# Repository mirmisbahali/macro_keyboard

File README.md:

# STM32 Macro Keyboard

A custom 6-key macro keyboard built from scratch custom written bare-metal STM32 firmware, hand-drawn schematics, and a PCB designed in KiCAD. No Arduino. No HAL. Just registers, datasheets, and stubbornness.

> **Status:** Hardware design in progress

---

*PCB layout and routing in progress.*

*Wiring is completed — schematic still needs to be made neat and tidy.*

<!-- Add photo of assembled board here -->
<!--  -->

---

## Why

I am learning to design STM32-based hardware - from choosing a microcontroller and designing the PCB, to writing drivers from scratch in register-level C.

## Hardware

| Item | Detail |
|---|---|
| MCU | STM32F072CBTx — Cortex-M0, 48 MHz, 128 KB flash, LQFP-48 |
| Key matrix | 6 switches with diode-per-key (1N4148W) |
| Power | 3.3 V core, ferrite bead on analog rail (VDDA), decoupling on all supply pins |
| Programming | USB DFU via BOOT0 SPDT switch — no debug probe needed |
| EDA tool | KiCAD 10.0 |

---

## Requirements

Requirements follow the systems engineering convention: **shall** = mandatory, **should** = desired.

### SYS — System
| ID | Requirement |
|---|---|
| SYS-01 | The device shall enumerate as a USB HID keyboard on any host OS without requiring driver installation. |
| SYS-02 | The device shall be powered entirely from the USB bus (5 V, ≤ 100 mA). |
| SYS-03 | The device shall support a minimum of 6 independently programmable macro keys. |
| SYS-04 | The device firmware shall be updatable via USB without a hardware debug probe. |
| SYS-05 | All firmware shall be written in register-level C with no vendor HAL or Arduino abstractions. |

### HW — Hardware
| ID | Requirement |
|---|---|
| HW-01 | The MCU core supply (VDD) shall be 3.3 V ± 5%. |
| HW-02 | Each VDD, VDDA, VBAT, and VSSIO2 supply pin shall have a dedicated decoupling capacitor placed within 2 mm of the pin. |
| HW-03 | VDDA shall be filtered from VDD using a ferrite bead to reduce digital noise on the analog supply. |
| HW-04 | Each key switch shall have a dedicated series diode to prevent ghosting in the key matrix. |
| HW-05 | The BOOT0 pin shall be switchable between VDD and GND via an SPDT switch to allow toggling between DFU programming mode and normal run mode. |
| HW-06 | The PCB shall pass KiCAD DRC with zero errors before submission for fabrication. |

### FW — Firmware
| ID | Requirement |
|---|---|
| FW-01 | The firmware shall configure the system clock to 48 MHz using the internal PLL before any peripheral initialisation. |
| FW-02 | The key scan loop shall debounce each key with a settling time of ≤ 5 ms. |
| FW-03 | The firmware shall report a key press to the USB host within 10 ms of a physical key actuation. |
| FW-04 | Macro key mappings shall be stored in non-volatile flash and survive a power cycle. |
| FW-05 | The firmware shall implement the USB HID boot-protocol keyboard descriptor to ensure compatibility with BIOS/UEFI environments. |

### VER — Verification
| ID | Requirement | Method |
|---|---|---|
| VER-01 | All supply rails measure within tolerance at board bring-up. | Test — multimeter |
| VER-02 | Device enumerates as HID keyboard on Windows, macOS, and Linux. | Test — plug in, check device manager |
| VER-03 | Every key registers a unique, correct HID keycode. | Test — key tester utility |
| VER-04 | Firmware can be flashed via DFU using only the BOOT0 switch and a USB cable. | Demonstration |
| VER-05 | Key mappings persist across power cycles. | Test — assign macro, power cycle, verify |
| VER-06 | PCB DRC passes with zero errors. | Analysis — KiCAD DRC report |

---

<details>
<summary><strong>Roadmap</strong></summary>

### Electronics
- [x] MCU symbol + footprint
- [x] Decoupling capacitors (VBAT, VDD, VDDA, VSSIO2)
- [x] BOOT0 SPDT switch for programming / run mode toggle
- [ ] USB data lines + ESD protection
- [ ] USB power input + 3.3 V regulator
- [ ] Key switch matrix (complete all 6 keys)
- [ ] PCB layout and routing
- [ ] DRC pass → Gerber export → fabrication

### Firmware
- [ ] Bare-metal project setup (linker script, startup file)
- [ ] System clock → 48 MHz via PLL
- [ ] GPIO driver — key matrix scan
- [ ] USB HID descriptor (boot-protocol keyboard)
- [ ] Key debounce
- [ ] Macro layer + flash storage for mappings

</details>

---

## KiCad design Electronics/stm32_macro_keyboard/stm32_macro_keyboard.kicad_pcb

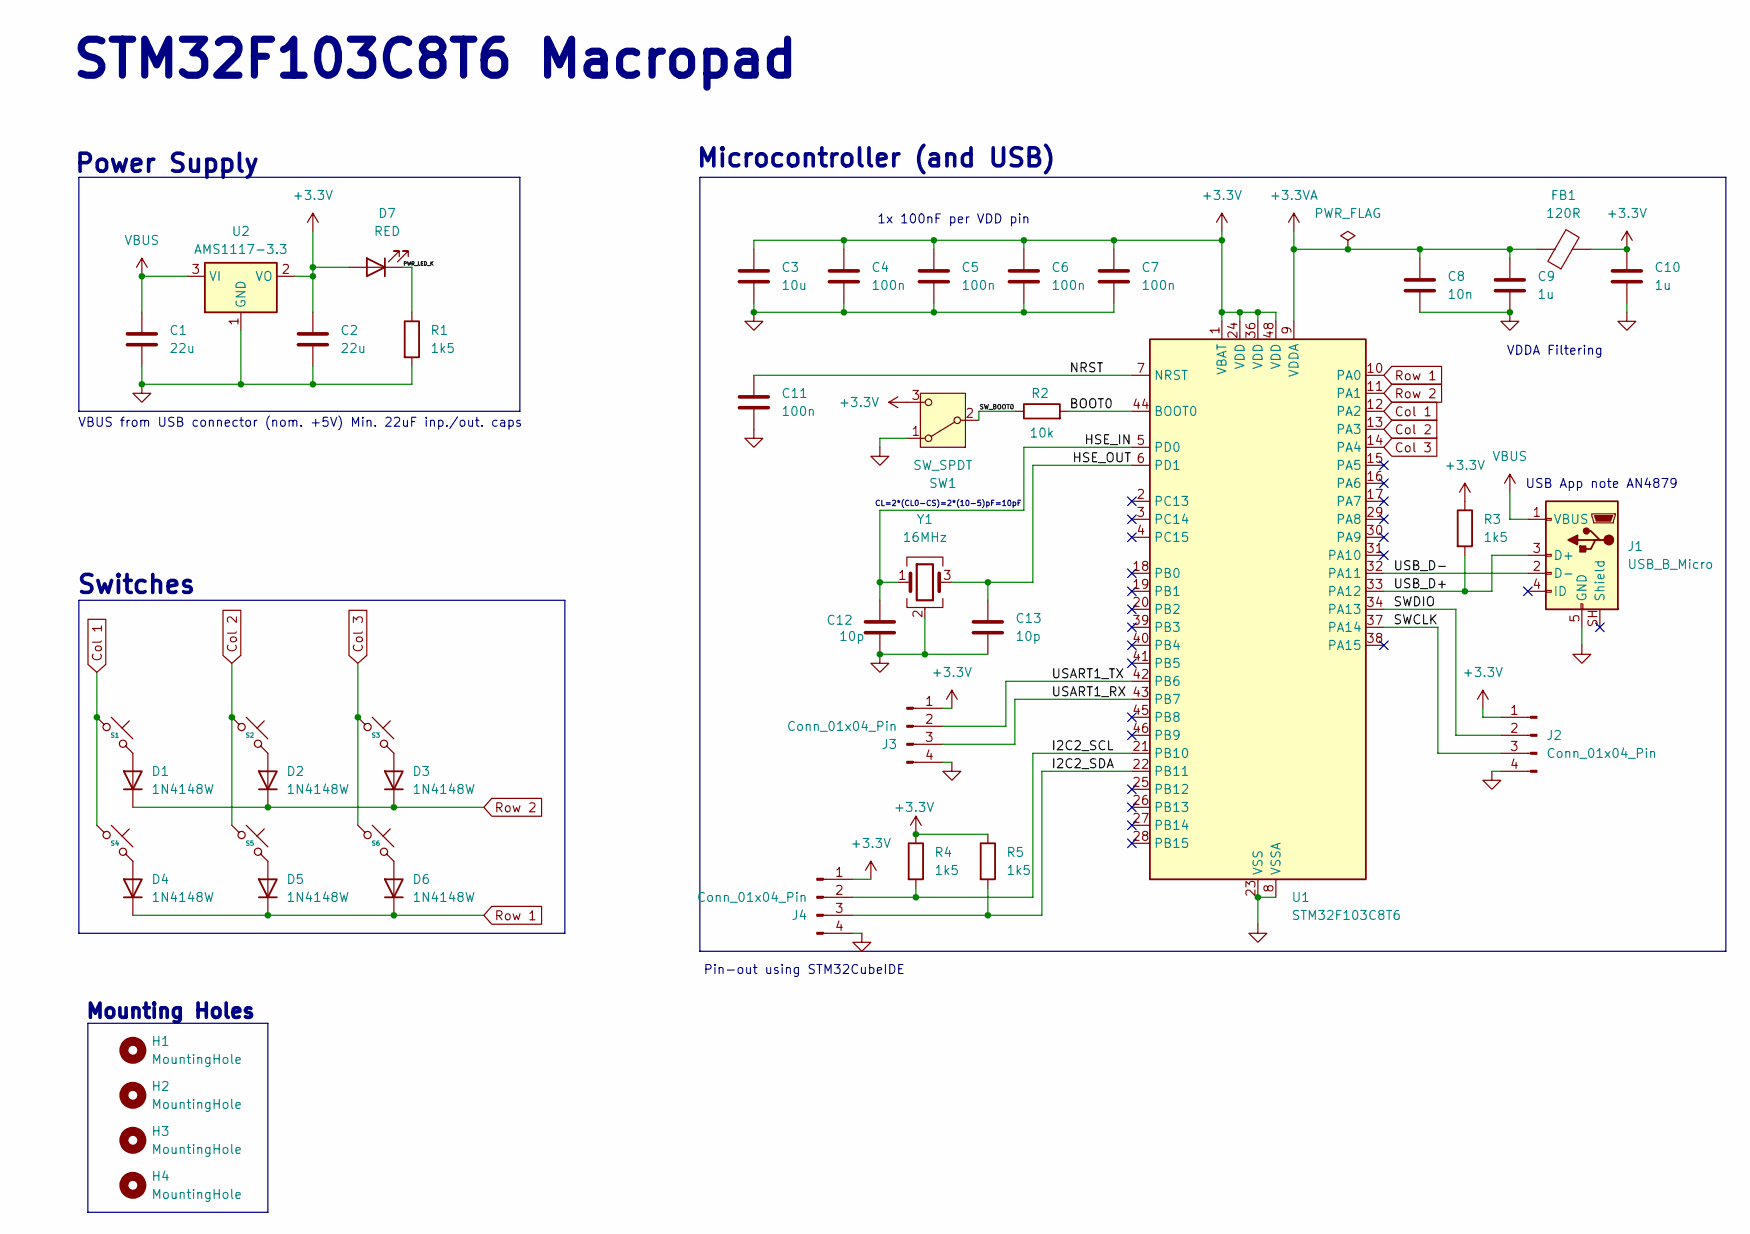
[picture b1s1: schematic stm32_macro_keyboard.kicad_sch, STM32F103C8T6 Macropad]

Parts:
C1, C2: 22u; C_0805_2012Metric
C3: 10u; C_0603_1608Metric
C4, C5, C6, C7, C11: 100n; C_0402_1005Metric
C8: 10n; C_0402_1005Metric
C9, C10: 1u; C_0402_1005Metric
C12, C13: 10p; C_0402_1005Metric
D1, D2, D3, D4, D5, D6: 1N4148W; D_SOD-123
D7: RED; LED_0603_1608Metric
FB1: 120R; L_0603_1608Metric
H1, H2, H3, H4: MountingHole; MountingHole_2.2mm_M2
J1: USB_B_Micro; USB_Micro-B_Wuerth_629105150521
J2, J3, J4: Conn_01x04_Pin; PinHeader_1x04_P2.54mm_Vertical
R1, R3, R4, R5: 1k5; R_0402_1005Metric
R2: 10k; R_0402_1005Metric
S1, S2, S3, S4, S5, S6: MX_PCB_2.50u
SW1: SW_SPDT; SW_SPDT_PCM12
U1: STM32F103C8T6; LQFP-48_7x7mm_P0.5mm
U2: AMS1117-3.3; SOT-223-3_TabPin2
Y1: 16MHz; Crystal_SMD_3225-4Pin_3.2x2.5mm

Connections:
+3.3V: C2.1, C3.1, C4.1, C5.1, C6.1, C7.1, C10.1, D7.2 (A), FB1.2, J2.1, J3.1, J4.1, R3.1, R4.1, R5.1, SW1.3 (C), U1.1 (VBAT), U1.24 (VDD), U1.36 (VDD), U1.48 (VDD), U2.2 (VO)
+3.3VA: C8.1, C9.1, FB1.1, U1.9 (VDDA)
/BOOT0: R2.2, U1.44 (BOOT0)
/HSE_IN: C12.1, U1.5 (PD0), Y1.1
/HSE_OUT: C13.1, U1.6 (PD1), Y1.3
/I2C2_SCL: J4.2, R4.2, U1.21 (PB10)
/I2C2_SDA: J4.3, R5.2, U1.22 (PB11)
/NRST: C11.1, U1.7 (NRST)
/PWR_LED_K: D7.1 (K), R1.1
/SWCLK: J2.3, U1.37 (PA14)
/SWDIO: J2.2, U1.34 (PA13)
/SW_BOOT0: R2.1, SW1.2 (B)
/USART1_RX: J3.3, U1.43 (PB7)
/USART1_TX: J3.2, U1.42 (PB6)
/USB_D+: J1.3 (D+), R3.2, U1.33 (PA12)
/USB_D-: J1.2 (D-), U1.32 (PA11)
Col 1: S1.1, S4.1, U1.12 (PA2)
Col 2: S2.1, S5.1, U1.13 (PA3)
Col 3: S3.1, S6.1, U1.14 (PA4)
GND: C1.2, C2.2, C3.2, C4.2, C5.2, C6.2, C7.2, C8.2, C9.2, C10.2, C11.2, C12.2, C13.2, J1.5 (GND), J2.4, J3.4, J4.4, R1.2, SW1.1 (A), U1.8 (VSSA), U1.23 (VSS), U1.35 (VSS), U1.47 (VSS), U2.1 (GND), Y1.2 (G), Y1.4 (G)
unnamed: D1.2 (A), S1.2
unnamed: D2.2 (A), S2.2
unnamed: D3.2 (A), S3.2
unnamed: D4.2 (A), S4.2
unnamed: D5.2 (A), S5.2
unnamed: D6.2 (A), S6.2
Row 1: D4.1 (K), D5.1 (K), D6.1 (K), U1.10 (PA0)
Row 2: D1.1 (K), D2.1 (K), D3.1 (K), U1.11 (PA1)
VBUS: C1.1, J1.1 (VBUS), U2.3 (VI)

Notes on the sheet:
Microcontroller (and USB)
Mounting Holes
VBUS from USB connector (nom. +5V) Min. 22uF inp./out. caps
STM32F103C8T6 Macropad
CL=2*(CL0-CS)=2*(10-5)pF=10pF
Switches
VDDA Filtering
1x 100nF per VDD pin
Pin-out using STM32CubeIDE
USB App note AN4879
Power Supply

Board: 2 copper layers, 44 parts (0 on the bottom side), 29 nets, no tracks yet.

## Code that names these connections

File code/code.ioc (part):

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Mcu.Name=STM32F103C(8-B)Tx
Mcu.Package=LQFP48
Mcu.UserName=STM32F103C8Tx
PA11.Mode=Device
PA11.Signal=USB_DM
PA12.Mode=Device
PA12.Signal=USB_DP
PA13.Mode=Serial_Wire
PA13.Signal=SYS_JTMS-SWDIO
PA14.Mode=Serial_Wire
PA14.Signal=SYS_JTCK-SWCLK
PB10.Mode=I2C
PB10.Signal=I2C2_SCL
PB11.Mode=I2C
PB11.Signal=I2C2_SDA
PB6.Mode=Asynchronous
PB6.Signal=USART1_TX
PB7.Mode=Asynchronous
PB7.Signal=USART1_RX
PD0-OSC_IN.Mode=HSE-External-Oscillator
PD0-OSC_IN.Signal=RCC_OSC_IN
PD1-OSC_OUT.Mode=HSE-External-Oscillator
PD1-OSC_OUT.Signal=RCC_OSC_OUT
board=custom

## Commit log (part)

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2026-04-18 Initial commit: KiCAD macropad project and .gitignore
2026-04-21 Add decoupling capacitors and BOOT0 SPDT switch for MCU power-up
    - Added decoupling capacitors on VBAT, VDD, VDDA, and VSSIO2 pins
    - Added SPDT switch on BOOT0 to toggle between programming and normal run mode
    - Completes all circuitry required to power up the STM32 microcontroller
    - Updated .gitignore to exclude KiCAD lock files and external_resources/
2026-04-21 Add README to track project progress
2026-04-23 Add net labels for USB, HSE oscillator, and SWD debug signals
    - USB_D- and USB_D+ labels connected to PA11/PA12 for full-speed USB
    - HSE_IN and HSE_OUT labels on PF0/PF1 for external crystal oscillator
    - SWDIO and SWCLK labels on PA13/PA14 for SWD debug interface
2026-04-23 Add 16 MHz HSE crystal oscillator circuit
    - Add Y1 (Crystal_GND24) 16 MHz crystal on PF0/PF1 (HSE_IN/HSE_OUT)
    - Add C11 and C12 (10pF) load capacitors for crystal oscillator
    - Add GND connection for crystal ground pins
2026-04-23 Add USB Micro B connector (J1) with power and data connections
    - Add J1 (USB_B_Micro) connector symbol
    - Connect D- and D+ to USB_D-/USB_D+ nets on PA11/PA12
    - Connect VBUS to VBUS power rail and GND pin to GND
    - Mark ID and Shield pins as no-connect
2026-04-25 Configure USB, SWD, and HSE pins in STM32CubeMX IOC file
    Assign PA11/PA12 for USB Device (DM/DP), PA13/PA14 for SWD debug
    (SWDIO/SWCLK), and PF0/PF1 for HSE external oscillator. Add USB and
    SYS IPs with SysTick. This wires the CubeMX model up to match the
    schematic-level connections already placed.
2026-04-25 Add SWD debug header (J2) and power symbols to schematic
    Add a 4-pin connector J2 for SWD debug access with +3.3V and GND power
    symbols. Route MCU SWD signals (SWDIO/SWCLK) to the new header via wires.
2026-04-25 Add 3.3V LDO power regulation circuit to schematic
    Adds the full USB 5V → 3.3V power supply sub-circuit required to power
    the STM32F072 MCU from the USB bus:
    - U2 (AMS1117-3.3, SOT-223): LDO regulator converting VBUS (5V) to
    +3.3V. Chosen for its wide availability, 1A output capability, and
    simple 3-pin SOT-223 footprint that is easy to hand-solder.
    - C13, C14 (22µF each): Bulk input and output bypass capacitors on the
2026-05-04 Add schematic images, begin PCB layout, and configure GPIO key matrix pins
    Electronics:
    - Added Electronics/img/ with a 3D PCB render (PNG) and schematic export (SVG)
    for use in the README and project documentation
    - Expanded kicad_pcb from a blank stub to a full board definition with layer
    stack, design rules, net classes, and initial component placement — PCB
    layout and routing now in active progress
